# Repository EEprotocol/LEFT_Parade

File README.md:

[Japanese docs](./README_ja.md)
# LEFT Parade Project

This is a so-called *left-hand device*.  
You can also use it with your right hand.  
It is intended for situations where you use a pen display tablet or similar device with one of your hand and want to trigger macros with the other hand.

## TL;DR

## Specifications
- Connectivity is **Bluetooth only**. Wired connections are not supported.  
  This limitation is due to the ESP32-C3; however, by using a board such as the ESP32-S3 that supports USB HID, wired operation can be implemented.
- A battery can be installed (3.7 V Li-ion).  
  Connect it directly to the battery terminals on the surface of the ESP32-C3.
- Up to **80 different macros** can be configured using simultaneous key presses  
  (Arduino IDE is required to configure the macros).
- ~~To enable the above behavior, commands are sent **when the key switch is released**, not when it is pressed.~~  
- 2 mode implimented switched by the push switch in the rotary encoder:
    1. **Combination Mode**
        In this mode, you can assign 80 macros for the combination of multiple keys. The command is send to PC when you release the keys.
    2. **Fast Attack Mode**
        The number of assignment decline to 8 (same as the number of keys), but the command is send when you push the keys. You can use this mode if you mind the delay.

## Bill of Materials
| Component | Price (JPY) |
|:-----------|------------:|
| PCB | 110 |
| Rotary encoder | 550 |
| Knob | 324 |
| ESP32-C3 | 1,080 |
| Keycap | 70 |
| Key socket | 160 |
| Key switch | 330 |
| Battery | 450 |
| (SN74HC139N) | 135 |
| DIP socket (8 × 2 rows) | 135 |
| **Total** | **3,344** |

## Installation  
### Hardware
#### Circuit Diagram

The annotation of the parts on the PCB corresponds to the circuit diagram.  
**I made a place for the LED D11, but system does not use it.**
#### soldering map

If you make this device as Left hand device, you solder on the parts surronded by **red and purple line**,
and If you make it as right hand device, solder on the parts with **purple and blue line**.
The component mounting side aligns with the side marked with the respective part indicators.

### Software
1. Install Arduino IDE on your PC, e.g.  
```yay -S arduino-ide```  

2. Install library [Mystfit/ESP32-BLE-CompositeHID](https://github.com/Mystfit/ESP32-BLE-CompositeHID).

3. Upload to `leftandmechv5_PCB/leftandmechv5_PCB.ino` to ESP32-C3.

## Macros
You can set the macro in the preamble of the `.ino` scripts.

```cpp
const uint8_t KC_SAVE[] = { 0x01, KEY_S };
const uint8_t KC_COPY[] = { 0x01, KEY_C };
const uint8_t KC_PASTE[] = { 0x01, KEY_V };
const uint8_t KC_DELETE[] = { 0x4c };
const uint8_t KC_m[] = { KEY_M };
const uint8_t KC_UNDO[] = { 0x01, KEY_Z };
const uint8_t KC_ESC[] = { KEY_ESC };
const uint8_t KC_UP[] = { KEY_UP };
const uint8_t KC_DOWN[] = { KEY_DOWN };
const uint8_t KC_LEFT[] = { KEY_LEFT };
const uint8_t KC_RIGHT[] = { KEY_RIGHT };
const uint8_t KC_PAGE_NEXT[] = { 0x01, KEY_RIGHT };
const uint8_t KC_PAGE_BACK[] = { 0x01, KEY_LEFT };
```
The list of `uint8_t` refers the operation s.t. Ctrl+S, ESC, or Delete. This list of macro is commonly used in the two mode.
In the list, terms of keys except the last term is regarded as modifier keys s.t. Alt, Ctrl or Shift.

### 1. Combination Mode
For this mode, you can set the assignment with `keymap[]`.
```cpp
const keyMapEntry keymap[] = {
  { 1, { KC_SAVE, 2 } },
  { 54, { KC_ESC, 1 } },
  { 4, { KC_COPY, 2 } },
  { 7, { KC_PASTE, 2 } },
  { 2, { KC_DELETE, 1 } },
  { 6, { KC_m, 1 } },
  { 28, { KC_UNDO, 2 } },
  { 18, { KC_UP, 1 } },
  { 9, { KC_DOWN, 1 } },
  { 27, { KC_LEFT, 1 } },
  { 3, { KC_RIGHT, 1 } },
  { 8, { KC_PAGE_NEXT, 2 } },
  { 20, { KC_PAGE_BACK, 2 } }
};
```

The first number refers the keyID of the combinaiton, second string refers the macro which you defined above and the last number refers the number of the element of the list of the macro. You can calculate the keyID as following:

2 refers the upper key, 1 refers the lower key, 0 refers no pushed.
In this mode, it is prohibited to push 2 keys in a column.

### 2. Fast Attack Mode
```cpp
const keyMapEntry direct_key[] = {
  { 1, { KC_LEFT, 1 } },
  { 2, { KC_UP, 1 } },
  { 3, { KC_DOWN, 1 } },
  { 5, { KC_RIGHT, 1 } }
};
```

The key ID which plades the first number corresponds to the following assignment:

## Todo
- [x] Impliment the GAME mode which sends commnad when keys are pushed
- [x] Fabricate a PCB
- [ ] Prepare the other version: RIGHT Parade

## Special Thanks
- [Mystfit/ESP32-BLE-CompositeHID](https://github.com/Mystfit/ESP32-BLE-CompositeHID)
- [freerouting/freerouting](https://github.com/freerouting/freerouting?tab=readme-ov-file)

## Contact
If you have something to ask, please mail to [keik4656@gmail.com](keik4656@gmail.com).

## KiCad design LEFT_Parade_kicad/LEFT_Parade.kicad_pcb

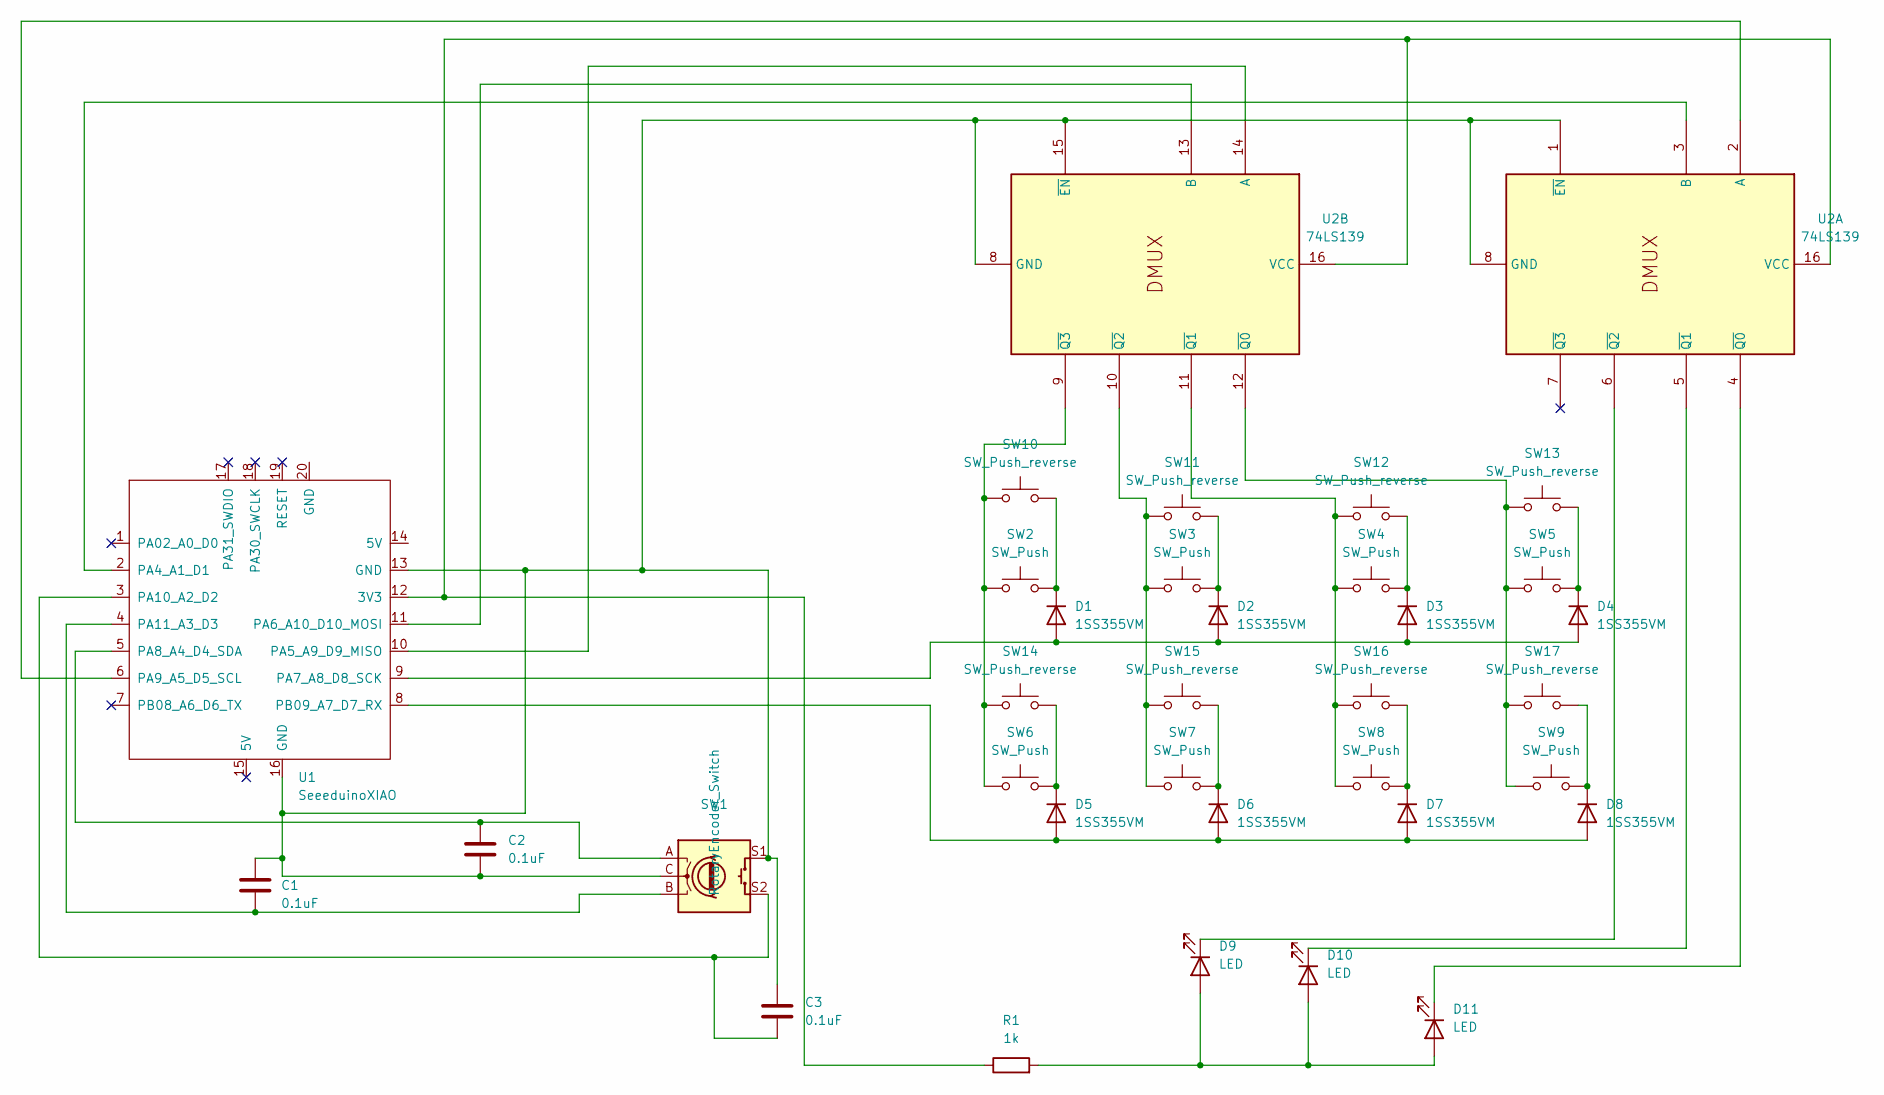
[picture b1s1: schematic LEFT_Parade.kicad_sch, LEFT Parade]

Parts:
C1, C2, C3: 0.1uF; C_Axial_L5.1mm_D3.1mm_P7.50mm_Horizontal
D1, D2, D3, D4, D5, D6, D7, D8: 1SS355VM; D_A-405_P7.62mm_Horizontal
D9, D10, D11: LED; LED_D3.0mm_Clear
R1: 1k; R_Axial_DIN0207_L6.3mm_D2.5mm_P10.16mm_Horizontal
SW1: RotaryEncoder_Switch; RotaryEncoder_Alps_EC12E-Switch_Vertical_H20mm
SW2, SW3, SW4, SW5, SW6, SW7, SW8, SW9: SW_Push; SW_Cherry_MX_1.00u_PCB
SW10, SW11, SW12, SW13, SW14, SW15, SW16, SW17: SW_Push_reverse; SW_Cherry_MX_1.00u_PCB_reverse
U1: SeeeduinoXIAO; ESP32C3_Footprint
U2: 74LS139; CERDIP-16_W7.62mm_SideBrazed

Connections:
unnamed: D1.2 (A), D2.2 (A), D3.2 (A), D4.2 (A), U1.9 (PA7_A8_D8_SCK)
unnamed: D1.1 (K), SW2.2, SW10.2
unnamed: D2.1 (K), SW3.2, SW11.2
unnamed: D3.1 (K), SW4.2, SW12.2
unnamed: D4.1 (K), SW5.2, SW13.2
unnamed: D5.2 (A), D6.2 (A), D7.2 (A), D8.2 (A), U1.8 (PB09_A7_D7_RX)
unnamed: D5.1 (K), SW6.2, SW14.2
unnamed: D6.1 (K), SW7.2, SW15.2
unnamed: D7.1 (K), SW8.2, SW16.2
unnamed: D8.1 (K), SW9.2, SW17.2
unnamed: D9.1 (K), U2.6 (~Q2)
unnamed: D9.2 (A), D10.2 (A), D11.2 (A), R1.2
unnamed: D10.1 (K), U2.5 (~Q1)
unnamed: D11.1 (K), U2.4 (~Q0)
unnamed: R1.1, U1.12 (3V3), U2.16 (VCC)
unnamed: U1.2 (PA4_A1_D1), U2.3 (B)
unnamed: U1.10 (PA5_A9_D9_MISO), U2.14 (A)
unnamed: U1.11 (PA6_A10_D10_MOSI), U2.13 (B)
unnamed: C2.1, SW1.A, U1.5 (PA8_A4_D4_SDA)
unnamed: U1.6 (PA9_A5_D5_SCL), U2.2 (A)
unnamed: C3.2, SW1.S2, U1.3 (PA10_A2_D2)
unnamed: C1.2, SW1.B, U1.4 (PA11_A3_D3)
unnamed: C1.1, C2.2, C3.1, SW1.C, SW1.S1, U1.13 (GND), U1.16 (GND), U2.1 (~EN), U2.8 (GND), U2.15 (~EN)
unnamed: SW5.1, SW9.1, SW13.1, SW17.1, U2.12 (~Q0)
unnamed: SW4.1, SW8.1, SW12.1, SW16.1, U2.11 (~Q1)
unnamed: SW3.1, SW7.1, SW11.1, SW15.1, U2.10 (~Q2)
unnamed: SW2.1, SW6.1, SW10.1, SW14.1, U2.9 (~Q3)

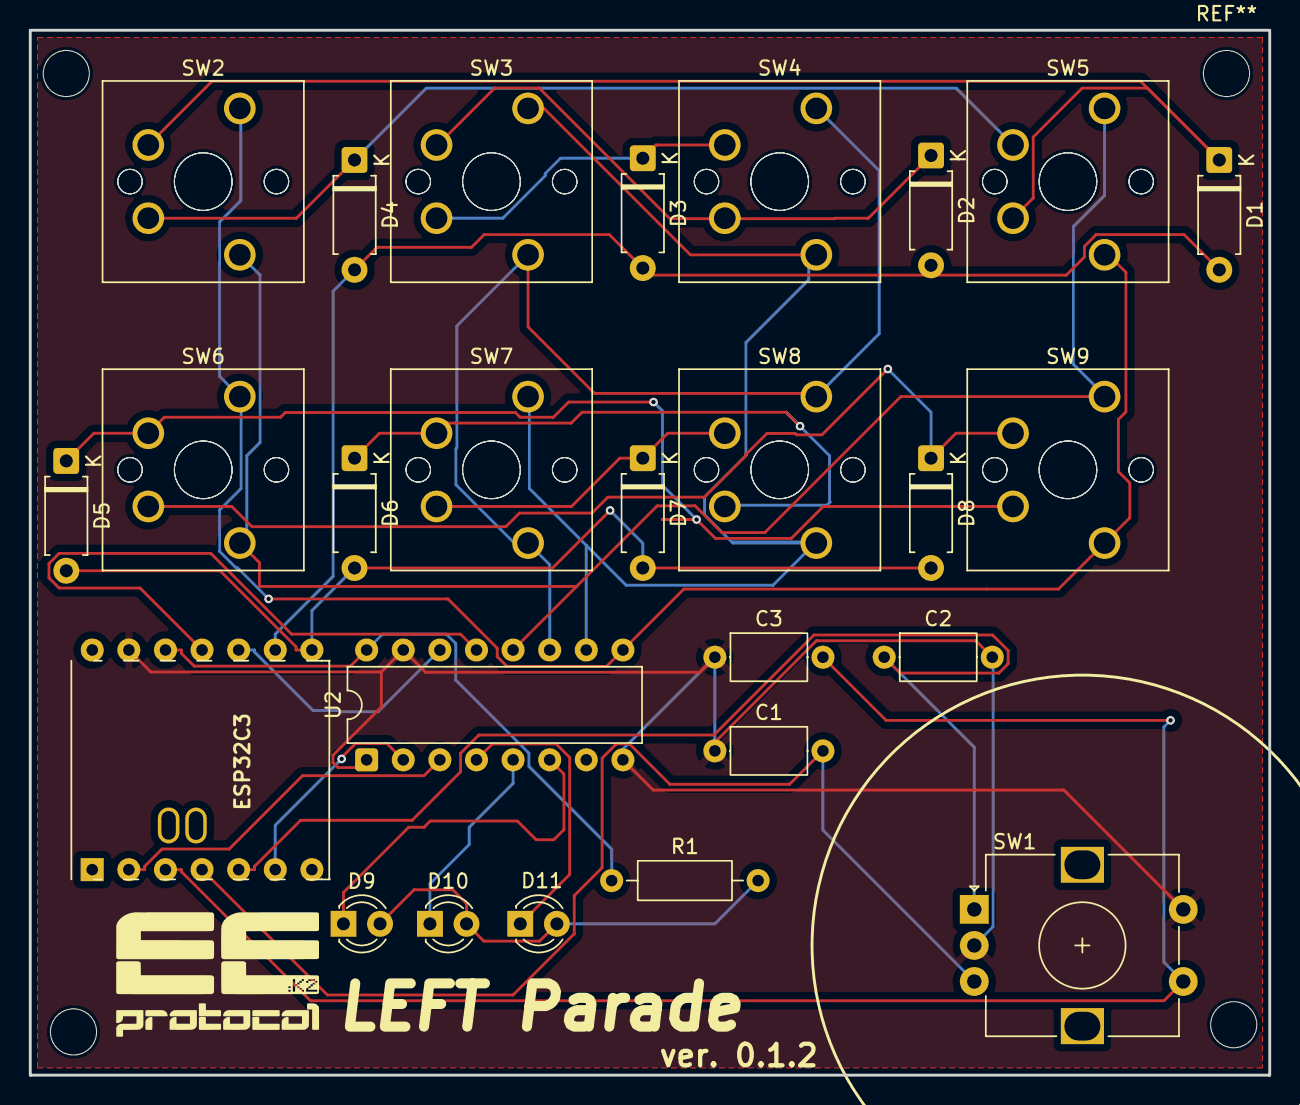
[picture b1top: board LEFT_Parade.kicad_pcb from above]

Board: 2 copper layers, 86.0 x 72.5 mm, 34 parts (0 on the bottom side), 27 nets.

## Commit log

2025-12-30 [Add] main file
2026-01-03 [Add] kicad project file
2026-01-05 [Add] Readme_Information
2026-01-05 [modify] Readme_Information
2026-01-09 [Add] Readme update
2026-01-12 [Add] game mode
2026-01-12 [MOdify] readme
2026-01-17 [modify] game mode operatin (turbo -> keep pushing)
2026-01-18 [Add] item in Readme
2026-01-19 [Add] movie
2026-01-19 [Modify] thankyou...
2026-01-21 [Modify] Readme.md
2026-01-22 [Modify] word
2026-02-15 [Modify] Version UP
2026-02-16 [Modify] Version UP on JP
2026-02-20 [Modify] solder.svg
2026-02-25 [Modify]
